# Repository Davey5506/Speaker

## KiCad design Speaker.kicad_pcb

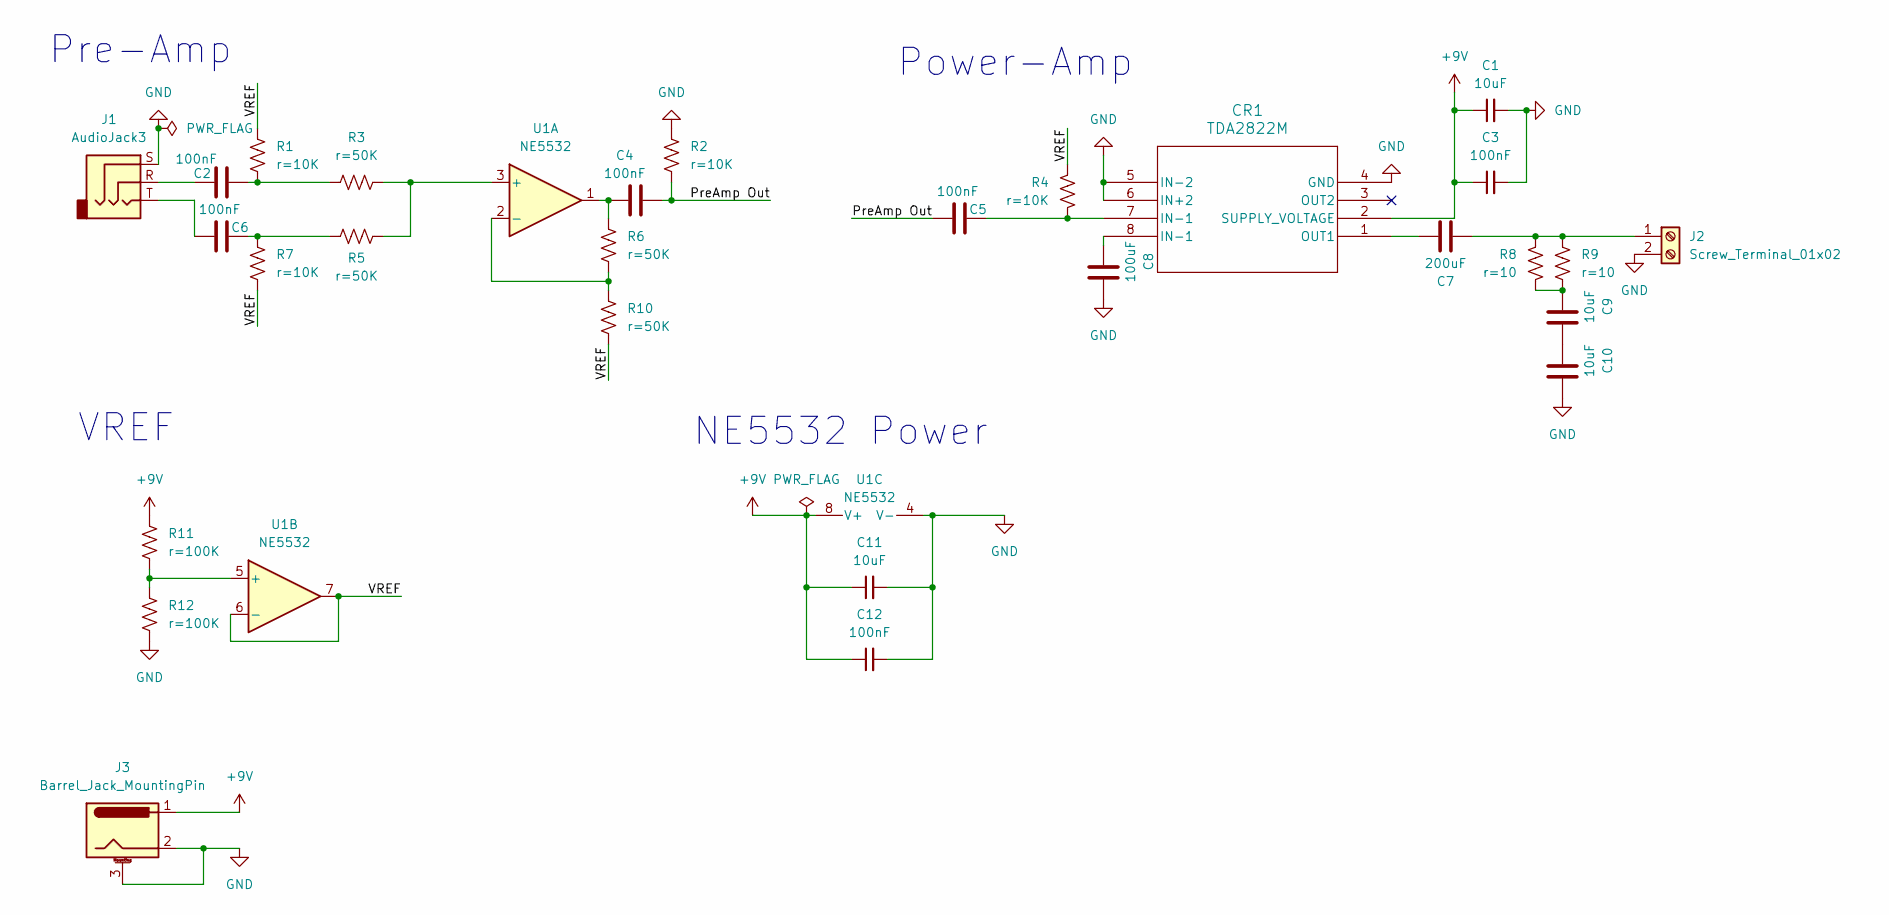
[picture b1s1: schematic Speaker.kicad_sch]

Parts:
C1, C9, C10, C11: 10uF; C_Radial_D6.3mm_H5.0mm_P2.50mm
C2, C3, C4, C5, C6, C12: 100nF; C_Disc_D3.0mm_W1.6mm_P2.50mm
C7: 200uF; C_Disc_D5.0mm_W2.5mm_P2.50mm
C8: 100uF; C_Radial_D6.3mm_H5.0mm_P2.50mm
CR1: TDA2822M; CERDIP-8_W7.62mm_SideBrazed_Socket
J1: AudioJack3; Jack_3.5mm_CUI_SJ1-3513N_Horizontal
J2: Screw_Terminal_01x02; TerminalBlock_MaiXu_MX126-5.0-02P_1x02_P5.00mm
J3: Barrel_Jack_MountingPin; BarrelJack_Horizontal
R1, R2, R4, R7: r=10K; R_Axial_DIN0204_L3.6mm_D1.6mm_P5.08mm_Horizontal
R3, R5, R6, R10: r=50K; R_Axial_DIN0204_L3.6mm_D1.6mm_P5.08mm_Horizontal
R8, R9: r=10; R_Axial_DIN0918_L18.0mm_D9.0mm_P22.86mm_Horizontal
R11, R12: r=100K; R_Axial_DIN0204_L3.6mm_D1.6mm_P5.08mm_Horizontal
U1: NE5532; CERDIP-8_W7.62mm_SideBrazed_Socket

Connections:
+9V: C1.1, C3.1, C11.1, C12.1, CR1.2 (SUPPLY_VOLTAGE), J3.1, R11.1, U1.8 (V+)
/PreAmp Out: C4.2, C5.1, R2.1
/VREF: R1.1, R4.2, R7.2, R10.1, U1.6 (-), U1.7
GND: C1.2, C3.2, C8.2, C10.2, C11.2, C12.2, CR1.4 (GND), CR1.5 (IN-2), CR1.6 (IN+2), J1.S, J2.2, J3.2, J3.3 (MountPin), R2.2, R12.2, U1.4 (V-)
unnamed: C2.1, J1.R
unnamed: C2.2, R1.2, R3.1
unnamed: C4.1, R6.2, U1.1
unnamed: C5.2, CR1.7 (IN-1), R4.1
unnamed: C6.1, J1.T
unnamed: C6.2, R5.1, R7.1
unnamed: C8.1, CR1.8 (IN-1)
unnamed: C9.1, R8.1, R9.1
unnamed: C9.2, C10.1
unnamed: C7.2, CR1.1 (OUT1)
unnamed: C7.1, J2.1, R8.2, R9.2
unnamed: R3.2, R5.2, U1.3 (+)
unnamed: R6.1, R10.2, U1.2 (-)
unnamed: R11.2, R12.1, U1.5 (+)

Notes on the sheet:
VREF
Power-Amp
NE5532 Power
Pre-Amp

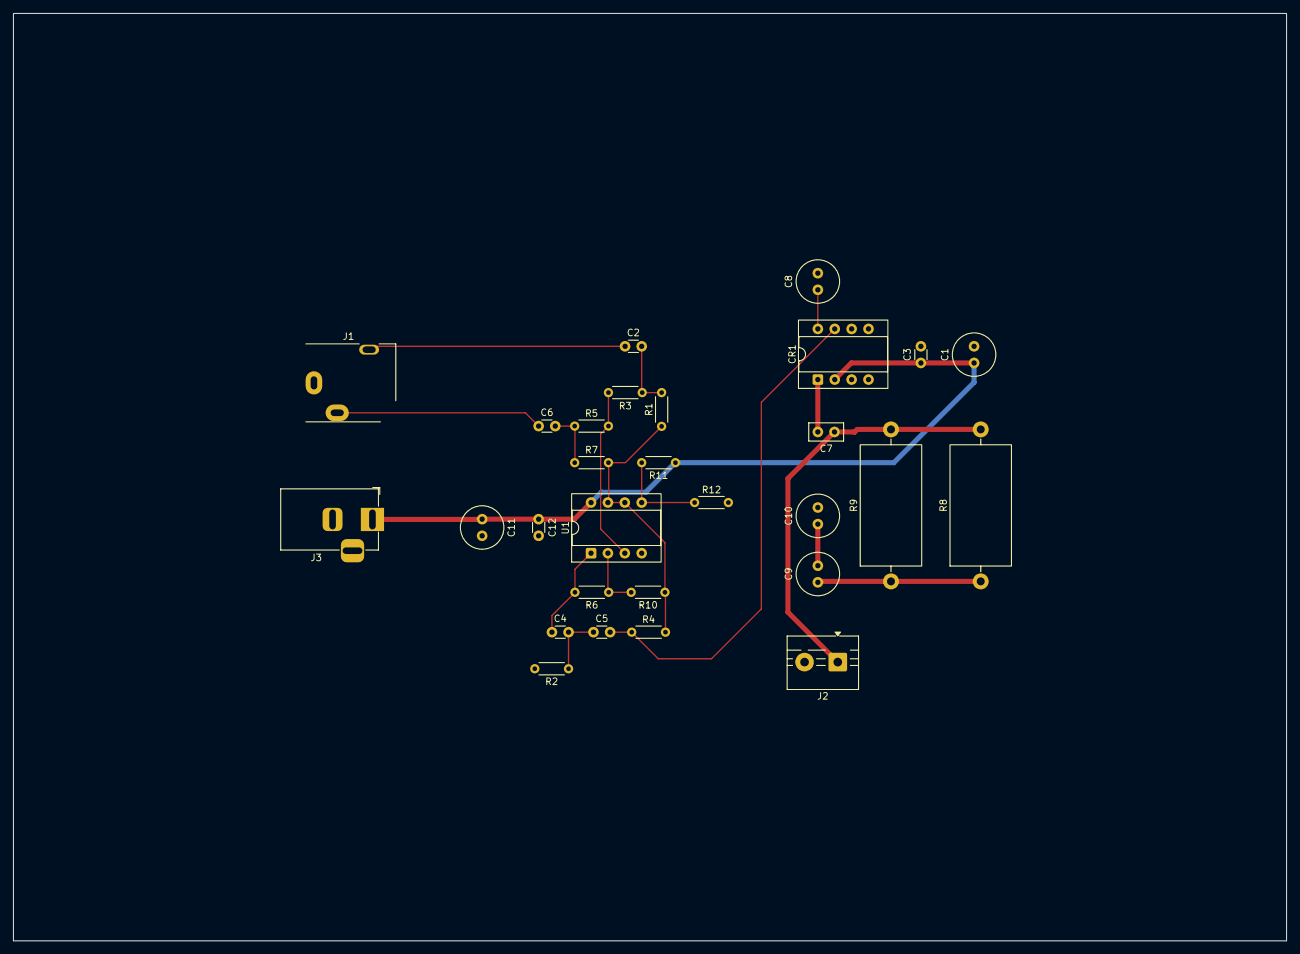
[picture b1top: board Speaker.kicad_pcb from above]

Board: 2 copper layers, 191.5 x 139.5 mm, 29 parts (0 on the bottom side), 18 nets.

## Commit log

2026-01-20 Inital commit
2026-01-20 Added power filtering for the NE5532
2026-01-20 Created PCB
2026-01-22 Updated exclusions
2026-01-22 Replaced TDA2282 with LM386 and the barrel jack with a switching varient.
